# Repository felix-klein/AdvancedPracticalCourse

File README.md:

## Advanced Practical Course

**Info text Part II - Advanced Practical Course:** \
This project is the continuation of the Bachelor: An Integrated Approach to Predictive
Maintenance and Quality Control for E-Engines through Compliance Checking. The Advanced Practical Course: 0000000917
Advanced Practical Course - Supportive Process Automation and Worker Assistance (IN2128, IN2106), offers the
possibility to extend and improve the prototype on specific features. The GitHub environment is used for this part II
of the project for reasons of overview and deployment. This is done by redeploying and embedding directly. Note that
much of the previous information, implementations and structures are retained, but their form can and must be changed.
A special tagging of the changed items is not made explicit, but can be taken from the git history.

**Info text Part I - Bachelor Thesis:** \
Welcome to the system and documentation environment for the bachelor thesis: An Integrated Approach to Predictive 
Maintenance and Quality Control for E-Engines through Compliance Checking. In addition to the written thesis, this work
also includes the practical part of the prototype construction. This environment is primarily used for editing and 
storing the software used for the prototype, but also includes the thesis itself, the literature references, the 
artefacts and a large number of images and videos that exceed the scope of the written work. In the following, you will
be referred to the further materials and receive information about the systems and environments used.

# Bachelor Thesis Material
All non-software related materials can be found in the folder [Bachelor-Thesis-Material](Bachelor-Thesis-Material).
* [Artefacts](Bachelor-Thesis-Material/Artefacts)\
  Artefacts include data sheets and implementation recommendations for the hardware, as well as software packages and 
  descriptions for the Infineon microcontroller.
* [Images](Bachelor-Thesis-Material/Images)\
  Images are divided into two sections: Images that can be found in the written elaboration and images that have been 
  added as supplements.
* [Literature References](Bachelor-Thesis-Material/Literature_References)\
  The literature references are copies of the literature used in the preparation of this thesis.
* [Written Thesis](Bachelor-Thesis-Material/Written_Thesis)\
  In the Written Thesis environment, you will find the written bachelor thesis in PDF format, as well as photographs of
  the submitted portfolio.

# Requirements for easy set up
For a simple setup of this project, [pom.xml](pom.xml) can be used,
the dependencies and plugins contained here are as follows:

* Dependencies:
    * javafx-controls
    * javafx-fxml
    * jSerialComm
* Plugins:
    * javafx-maven-plugin
* Properties:
    * maven.compiler.source: 20
    * maven.compiler.target: 20
    * project.build.sourceEncoding: UTF-8

# IDE's and external usages
* External IDE`s:
  * Camunda Modeler (Version 5.12.0)
  * Arduino IDE (Version 2.2.1)
  * Gluon — Scene Builder (Version 20.0.0)
  * IntelliJ IDEA — Ultimate Edition (Version 2023.2.1)
  * CLion (Version 2023.2.1)
  * Postman (Version 10.19.0)

* External Additions:
  * [CPEE](https://cpee.org/) - Engine: Modeller for the processes
  * Google Chrome (Version 117.0.5938.149) - As standard browser

# Build and run the project
To get the project running:
1. Install Google Chrome;
2. Make *Maven* executable (run) by use of:\
   ```View > Tool Windows > Maven > i17BA > Run Configurations > i17BA [javafx:run]```

# Code structure and layout
The code structure in the form of classes, methods and attributes can quickly become confusing in such large projects.
Therefore, the following lightweight UML-diagram reveals a structural representation of the back-end. Even though not
all methods (and even classes) are shown, it still illustrates the key connections.

# Commands and Sensor Response rules and syntax
* Commands:
  * STI (Sensor-Time-Interval): ->sensorInterval
  * EST (Engine-Status-Type): 0/1
  * HDA (Hall-Delay-Angle): 1-59
  * RPM (Rotations-per-Minute): 0-4000
  * TMD (Time-Duration): 0-int (in seconds)
  * EMS (Emergency Stop): 1 -> Description at [Emergency Stop](#Emergency-Stop)
* Sensor Response:
  * TMP is a list of all the Temperature gathered.
  * VIB is a list of all the Vibration gathered.
  * MIC is a list of all the Microphone levels of loudness gathered.
  * CP1 is a list of all the sensor values at the Current-Phase-1.
  * CP2 is a list of all the sensor values at the Current-Phase-2.
  * CP3 is a list of all the sensor values at the Current-Phase-3.
  * TSP is a list of all the respective Time-Stamps gathered.
  * MIS is a list of all the Mission-Initialisation-Stamps (not corresponding to the rest).

# Blueprint hardware command initialisation (data structure)
* Pre-Testing (Each 1 - 9):
  * Cold_Start_Fast
  * Long_Run
  * Cool_Down_Fast
  * Cold_Start_Slow&G_C_Up
  * Cool_Down_Slow&G_C_Down
* See command structure and description in
  [BlueprintCommandFlowHardware_Described](src/main/resources/adminFiles/BlueprintCommandFlowHardware_Described.txt)

# Comment structure 
Comments are an important and essential part of clear and comprehensible code. Therefor, we do integrate comments
whenever there is a line of code which is not trivial.\
For further clarification and as a result of active programming we decided to use two types to comments:\
  * `//` for not completed comments and work, like a 'in construction comment'
  * `/* */` and `/** **/`for final comments and work, like a 'final/normal comment'
This structure does not count for code which is not written in java.

# List of Programming-References
* Arduino IDE-language: [Arduino LANGUAGE](https://www.arduino.cc/reference/en/)
* Arduino API List: [Arduino List Library  2.1.4](https://nkaaf.github.io/Arduino-List/html/index.html)
* Infineon Shield Examples: [Example Sketches](Bachelor-Thesis-Material/Artefacts/TLE9879QXA40/02_example_sketches)

# Design Guide
* Main Design-Guide reference:
  * [M2-Material Design](https://m2.material.io/design/color/dark-theme.html)
* Color Scheme Dark-Theme:
  * Color Scheme: [TUM Colors](https://gist.github.com/lnksz/51e3566af2df5c7aa678cd4dfc8305f7)
  * Dark Scheme: [MATERIAL DESIGN - Dark theme](https://m2.material.io/design/color/dark-theme.html#ui-application)
    * Dark: `#121212` - Background
    * TUM Blue: `#0065bd` - Header
    * tum-blue-dark: `#072140` - 
    * tum-grey-1: `#20252A` - Box
    * Red200: `#B00020` `176,0,32` - Warning, Wrong Task
    * Green200: `#018786` `1, 135, 134`- Correct Task
    * tum-blue-light: `#5E94D4` - Label, Event Start/End
    * tum-blue-light-dark: `#9ABCE4` - Event

# Hardware Connection
* Connection:
  * Type: `Cable`
  * Technique: `Serial` (JSerialComm)
  * Port: `/dev/cu.usbmodem141101`
  * Baud Rate: `9600`
  * Terminal Input: `screen /dev/cu.usbmodem141101 115200`
  * Main information Link: [JSerial GitHub](https://github.com/Fazecast/jSerialComm)

# Emergency Stop
The Emergency Stop is a Task which can be included into a process when ever needed.
Its primary function and intended use is the testing of a process flow. The user does
not need to delete or create a new whole process just for the testing of a beginning segment.

The Emergency Stop functions as a rapid and immediate end of the test. No more commands are
transferred to the board, the motor will stop running and the sensor data will stop sending.

# Further Code Insights as a Guest
As the main Git environment for the generation of this project, the [LRZ GitLab](https://gitlab.lrz.de)
is in use. Included is an extensive documentation of Commit, Push and Merge commands, as well as 
Milestones and Labels.\
As the publication requires a public availability of the system code and additional materials, the transit
to [GitHub i17ba](https://github.com/felix-klein/i17ba) was conducted and does not include properties which are not 
regarded directly to the systems, e.g. Push history and Milestones.\
If you are interested in further insights, older releases or development stages which are documented in the GitLab
version of this project, or if you got general project question, please use the 
Discord-Server: [Server i17ba-Q&A](https://discord.gg/rDpUg3Vh) (active until one year after official project completion, 15.10.2023).

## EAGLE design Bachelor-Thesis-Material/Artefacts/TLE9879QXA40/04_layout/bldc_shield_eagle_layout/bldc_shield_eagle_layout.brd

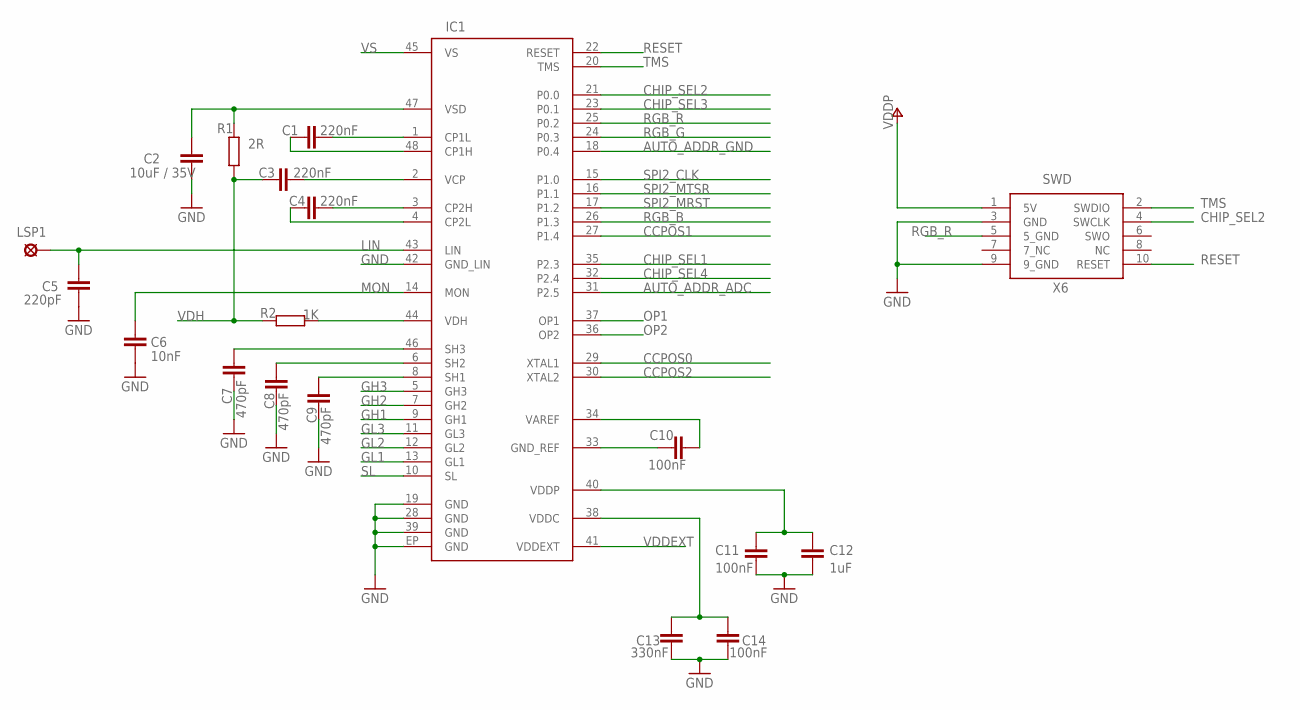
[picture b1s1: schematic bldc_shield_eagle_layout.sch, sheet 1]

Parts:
C1, C3, C4: 220nF; C0603
C2: 10uF / 35V; C1210; FARNELL 2112703RL
C5: 220pF; C0603
C6: 10nF; C0603
C7, C8, C9: 470pF; C0603
C10, C11, C14: 100nF; C0603
C12: 1uF; C0603
C13: 330nF; C0603
IC1: PROTEUS_EAGLE_TLE9879QX; VQFN48-15_7X7
INFINEONLOGO: INFINEON5; INFINEON_LOGO_5
LSP1: MCS10B
R1: 2R; R0603
R2: 1K; R0603
X6: SWD; FTSH-105-01-L-DH

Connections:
AUTO_ADDR_ADC: IC1.31 (P2.5); also elsewhere on the board
AUTO_ADDR_GND: IC1.18 (P0.4); also elsewhere on the board
CCPOS0: IC1.29 (XTAL1); also elsewhere on the board
CCPOS1: IC1.27 (P1.4); also elsewhere on the board
CCPOS2: IC1.30 (XTAL2); also elsewhere on the board
CHIP_SEL1: IC1.35 (P2.3); also elsewhere on the board
CHIP_SEL2: IC1.21 (P0.0), X6.4 (SWCLK); also elsewhere on the board
CHIP_SEL3: IC1.23 (P0.1); also elsewhere on the board
CHIP_SEL4: IC1.32 (P2.4); also elsewhere on the board
CP1H: C1.2, IC1.48 (CP1H)
CP1L: C1.1, IC1.1 (CP1L)
CP2H: C4.1, IC1.3 (CP2H)
CP2L: C4.2, IC1.4 (CP2L)
GH1: IC1.9 (GH1); also elsewhere on the board
GH2: IC1.7 (GH2); also elsewhere on the board
GH3: IC1.5 (GH3); also elsewhere on the board
GL1: IC1.13 (GL1); also elsewhere on the board
GL2: IC1.12 (GL2); also elsewhere on the board
GL3: IC1.11 (GL3); also elsewhere on the board
GND: C2.2, C5.1, C6.1, C7.2, C8.1, C9.1, C11.1, C12.1, C13.1, C14.1, IC1.19 (GND), IC1.28 (GND), IC1.39 (GND), IC1.42 (GND_LIN), IC1.EP (GND), X6.3 (GND), X6.9 (9_GND); also elsewhere on the board
GND_REF: C10.1, IC1.33 (GND_REF)
LIN: C5.2, IC1.43 (LIN), LSP1.MP
MON: C6.2, IC1.14 (MON)
OP1: IC1.37 (OP1); also elsewhere on the board
OP2: IC1.36 (OP2); also elsewhere on the board
RESET: IC1.22 (RESET), X6.10 (RESET); also elsewhere on the board
RGB_B: IC1.26 (P1.3); also elsewhere on the board
RGB_G: IC1.24 (P0.3); also elsewhere on the board
RGB_R: IC1.25 (P0.2), X6.5 (5_GND); also elsewhere on the board
SH1: C9.2, IC1.8 (SH1); also elsewhere on the board
SH2: C8.2, IC1.6 (SH2); also elsewhere on the board
SH3: C7.1, IC1.46 (SH3); also elsewhere on the board
SL: IC1.10 (SL); also elsewhere on the board
SPI2_CLK: IC1.15 (P1.0); also elsewhere on the board
SPI2_MRST: IC1.17 (P1.2); also elsewhere on the board
SPI2_MTSR: IC1.16 (P1.1); also elsewhere on the board
TMS: IC1.20 (TMS), X6.2 (SWDIO)
VAREF: C10.2, IC1.34 (VAREF)
VCP: C3.1, IC1.2 (VCP); also elsewhere on the board
VDDC: C13.2, C14.2, IC1.38 (VDDC)
VDDEXT: IC1.41 (VDDEXT); also elsewhere on the board
VDDP: C11.2, C12.2, IC1.40 (VDDP), X6.1 (5V); also elsewhere on the board
VDH: C3.2, R1.2, R2.2; also elsewhere on the board
VDH_CHIP: IC1.44 (VDH), R2.1
VS: IC1.45 (VS); also elsewhere on the board
VSD: C2.1, IC1.47 (VSD), R1.1

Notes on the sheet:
RGB_R

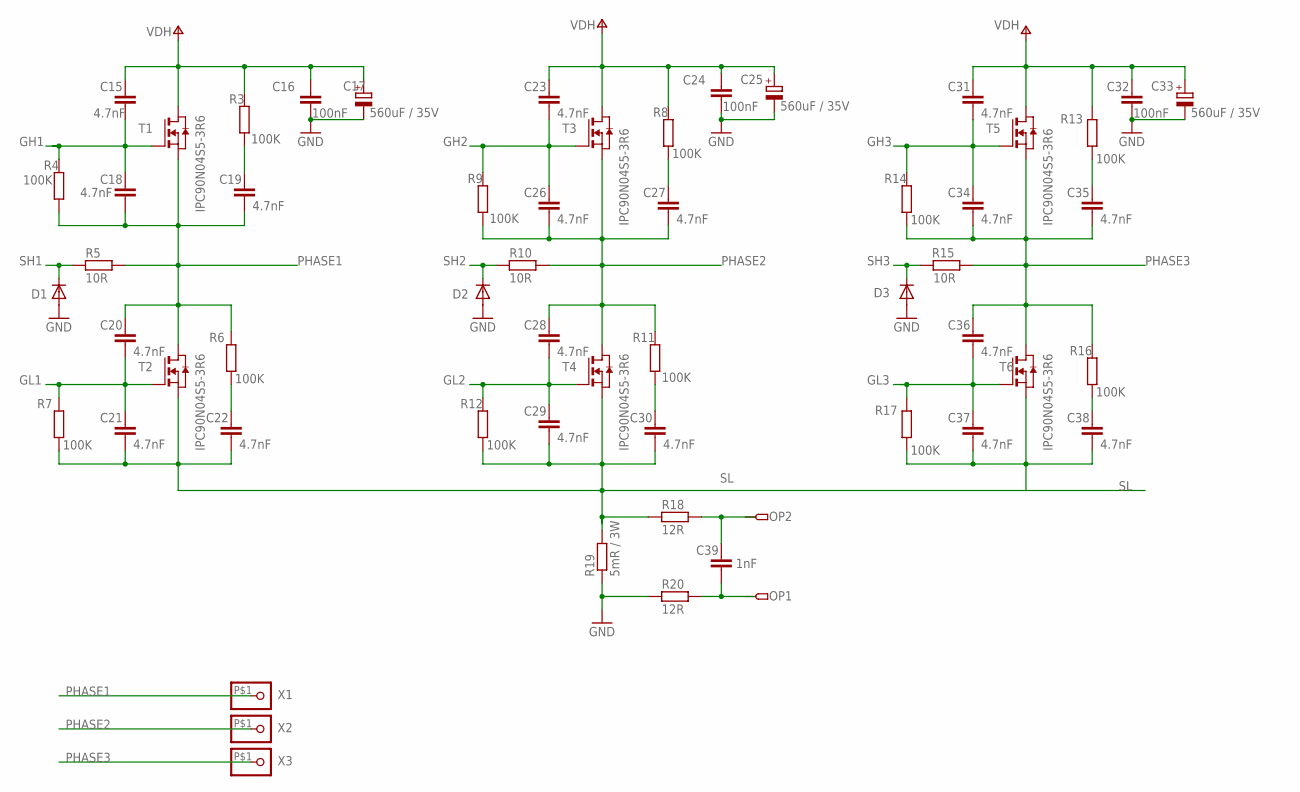
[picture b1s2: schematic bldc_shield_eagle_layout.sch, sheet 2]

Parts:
C15, C18, C19, C20, C21, C22, C23, C26, C27, C28, C29, C30, C31, C34, C35, C36, C37, C38: 4.7nF; C0603
C16, C24, C32: 100nF; C0603
C17, C25, C33: 560uF / 35V; 153CLV-1014; FARNELL 2408677
C39: 1nF; C0603
D1, D2, D3: DIODE-SOD323-W; SOD323-W
R3, R4, R6, R7, R8, R9, R11, R12, R13, R14, R16, R17: 100K; R0603
R5, R10, R15: 10R; R0603
R18, R20: 12R; R0603
R19: 5mR / 3W; R6332
T1, T2, T3, T4, T5, T6: IPC90N04S5-3R6; PG-TDSON-8
X1, X2, X3: SCREWHOLE

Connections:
GH1: C15.2, C18.1, R4.2, T1.4 (G); also elsewhere on the board
GH2: C23.2, C26.1, R9.2, T3.4 (G); also elsewhere on the board
GH3: C31.2, C34.1, R14.2, T5.4 (G); also elsewhere on the board
GL1: C20.2, C21.1, R7.2, T2.4 (G); also elsewhere on the board
GL2: C28.2, C29.1, R12.2, T4.4 (G); also elsewhere on the board
GL3: C36.2, C37.1, R17.2, T6.4 (G); also elsewhere on the board
GND: C16.2, C17.-, C24.2, C25.-, C32.2, C33.-, D1.A, D2.A, D3.A, R19.1, R20.2; also elsewhere on the board
unnamed: C19.1, R3.1
unnamed: C22.1, R6.1
unnamed: C27.1, R8.1
unnamed: C30.1, R11.1
unnamed: C38.1, R16.1
unnamed: C35.1, R13.1
OP1: C39.2, R20.1; also elsewhere on the board
OP2: C39.1, R18.1; also elsewhere on the board
PHASE1: C18.2, C19.2, C20.1, R4.1, R5.1, R6.2, T1.1 (S), T1.2 (S), T1.3 (S), T2.5 (D), T2.6 (D), T2.7 (D), T2.8 (D), T2.D, X1.P$1
PHASE2: C26.2, C27.2, C28.1, R9.1, R10.1, R11.2, T3.1 (S), T3.2 (S), T3.3 (S), T4.5 (D), T4.6 (D), T4.7 (D), T4.8 (D), T4.D, X2.P$1
PHASE3: C34.2, C35.2, C36.1, R14.1, R15.1, R16.2, T5.1 (S), T5.2 (S), T5.3 (S), T6.5 (D), T6.6 (D), T6.7 (D), T6.8 (D), T6.D, X3.P$1
SH1: D1.C, R5.2; also elsewhere on the board
SH2: D2.C, R10.2; also elsewhere on the board
SH3: D3.C, R15.2; also elsewhere on the board
SL: C21.2, C22.2, C29.2, C30.2, C37.2, C38.2, R7.1, R12.1, R17.1, R18.2, R19.2, T2.1 (S), T2.2 (S), T2.3 (S), T4.1 (S), T4.2 (S), T4.3 (S), T6.1 (S), T6.2 (S), T6.3 (S); also elsewhere on the board
VDH: C15.1, C16.1, C17.+, C23.1, C24.1, C25.+, C31.1, C32.1, C33.+, R3.2, R8.2, R13.2, T1.5 (D), T1.6 (D), T1.7 (D), T1.8 (D), T1.D, T3.5 (D), T3.6 (D), T3.7 (D), T3.8 (D), T3.D, T5.5 (D), T5.6 (D), T5.7 (D), T5.8 (D), T5.D; also elsewhere on the board

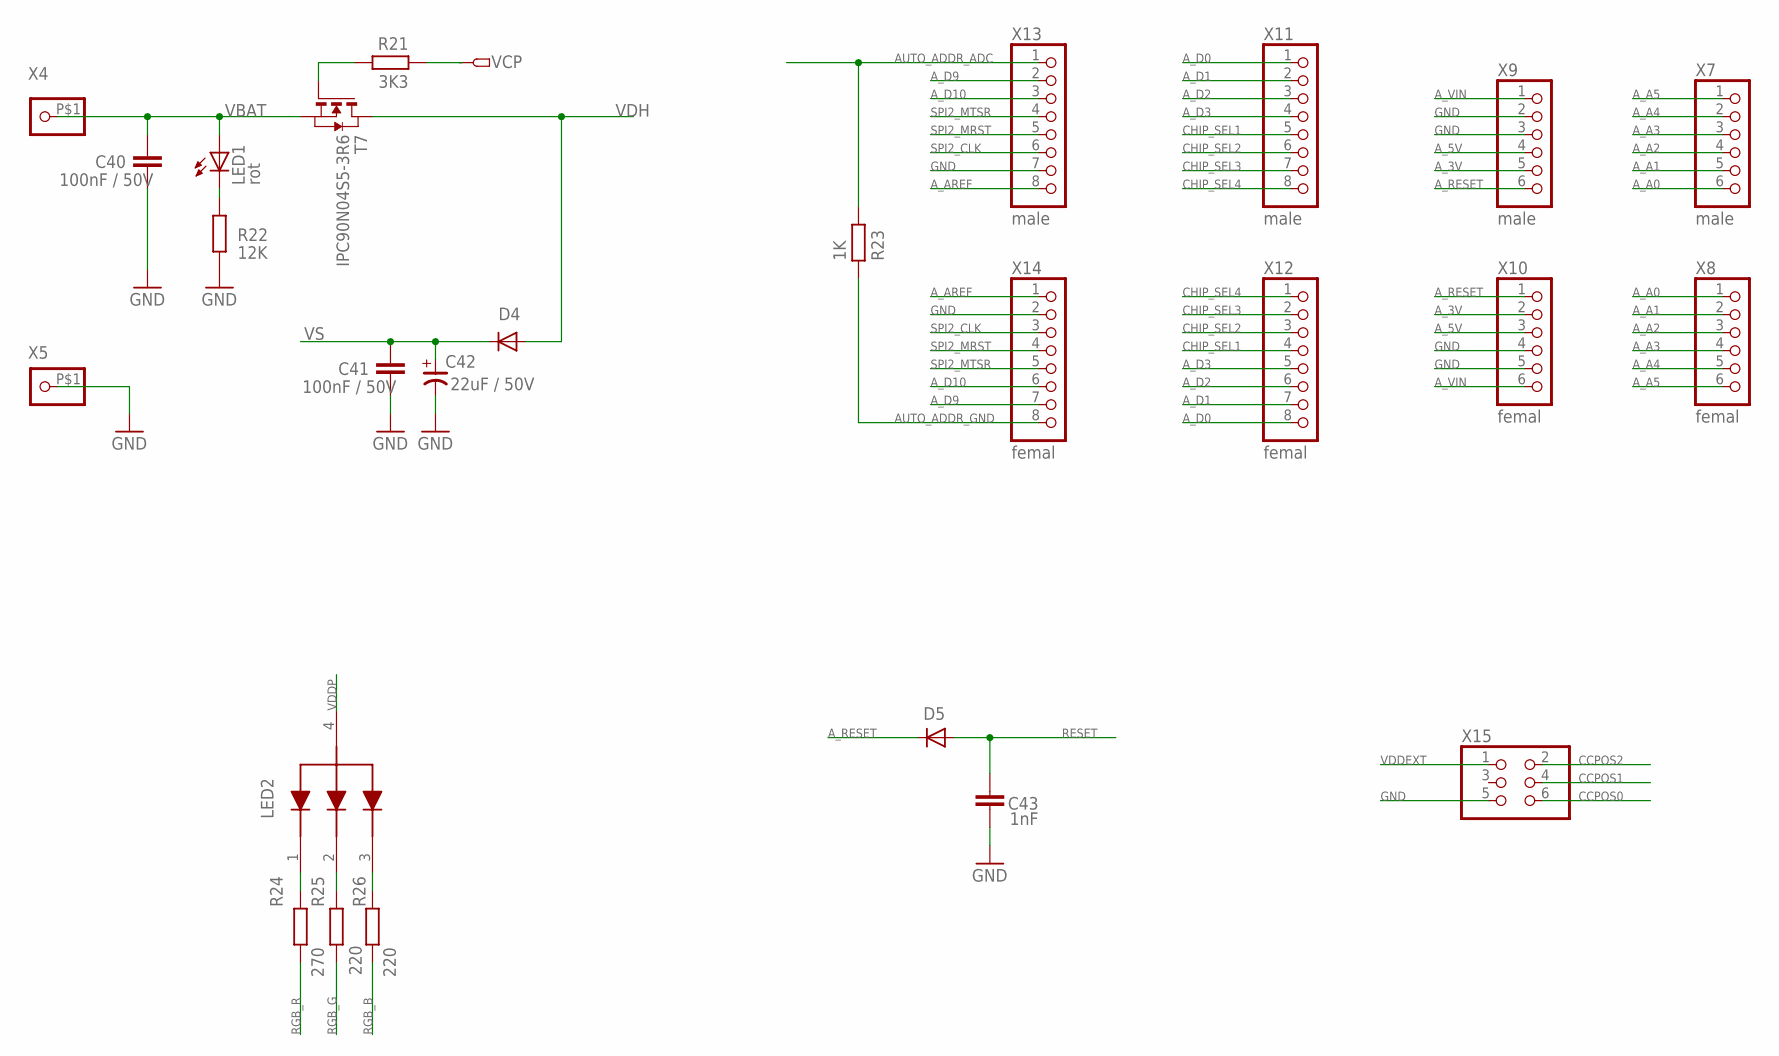
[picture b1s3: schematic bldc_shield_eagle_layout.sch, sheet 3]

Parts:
C40, C41: 100nF / 50V; C0603; FARNELL 1740621
C42: 22uF / 50V; 153CLV-0505; FARNELL 2408669
C43: 1nF; C0603
D4: DIODE_DIODE-SOD123; DIODE_SOD123
D5: DIODE-SOD323-W; SOD323-W
LED1: rot; SML0603; FARNELL 2112124
LED2: RGB_LED; LTST-C19HE1WT
R21: 3K3; R0603
R22: 12K; R0603
R23: 1K; R0603
R24: 270; R0603
R25, R26: 220; R0603
T7: IPC90N04S5-3R6; PG-TDSON-8
X4, X5: SCREWHOLE
X7, X9: male; 1X06SMD
X8, X10: femal; 1X06SMD-FEMAL
X11, X13: male; 1X08SMD
X12, X14: femal; 1X08SMD-FEMAL
X15: PINHD-2X3_2.54-90°; 2X03/90

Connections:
AUTO_ADDR_ADC: R23.2, X13.1; also elsewhere on the board
AUTO_ADDR_GND: R23.1, X14.8; also elsewhere on the board
A_3V: X9.5, X10.2
A_5V: X9.4, X10.3
A_A0: X7.6, X8.1
A_A1: X7.5, X8.2
A_A2: X7.4, X8.3
A_A3: X7.3, X8.4
A_A4: X7.2, X8.5
A_A5: X7.1, X8.6
A_AREF: X13.8, X14.1
A_D0: X11.1, X12.8
A_D1: X11.2, X12.7
A_D2: X11.3, X12.6
A_D3: X11.4, X12.5
A_D9: X13.2, X14.7
A_D10: X13.3, X14.6
A_RESET: D5.C, X9.6, X10.1
A_VIN: X9.1, X10.6
CCPOS0: X15.6; also elsewhere on the board
CCPOS1: X15.4; also elsewhere on the board
CCPOS2: X15.2; also elsewhere on the board
CHIP_SEL1: X11.5, X12.4; also elsewhere on the board
CHIP_SEL2: X11.6, X12.3; also elsewhere on the board
CHIP_SEL3: X11.7, X12.2; also elsewhere on the board
CHIP_SEL4: X11.8, X12.1; also elsewhere on the board
GND: C40.2, C41.2, C42.-, C43.1, R22.2, X5.P$1, X9.2, X9.3, X10.4, X10.5, X13.7, X14.2, X15.5; also elsewhere on the board
unnamed: LED2.2, R25.1
unnamed: LED2.1, R24.1
unnamed: LED2.3, R26.1
unnamed: R21.2, T7.4 (G)
unnamed: LED1.C, R22.1
RESET: C43.2, D5.A; also elsewhere on the board
RGB_B: R26.2; also elsewhere on the board
RGB_G: R25.2; also elsewhere on the board
RGB_R: R24.2; also elsewhere on the board
SPI2_CLK: X13.6, X14.3; also elsewhere on the board
SPI2_MRST: X13.5, X14.4; also elsewhere on the board
SPI2_MTSR: X13.4, X14.5; also elsewhere on the board
VBAT: C40.1, LED1.A, T7.1 (S), T7.2 (S), T7.3 (S), X4.P$1
VCP: R21.1; also elsewhere on the board
VDDEXT: X15.1; also elsewhere on the board
VDDP: LED2.4; also elsewhere on the board
VDH: D4.A, T7.5 (D), T7.6 (D), T7.7 (D), T7.8 (D), T7.D; also elsewhere on the board
VS: C41.1, C42.+, D4.C; also elsewhere on the board

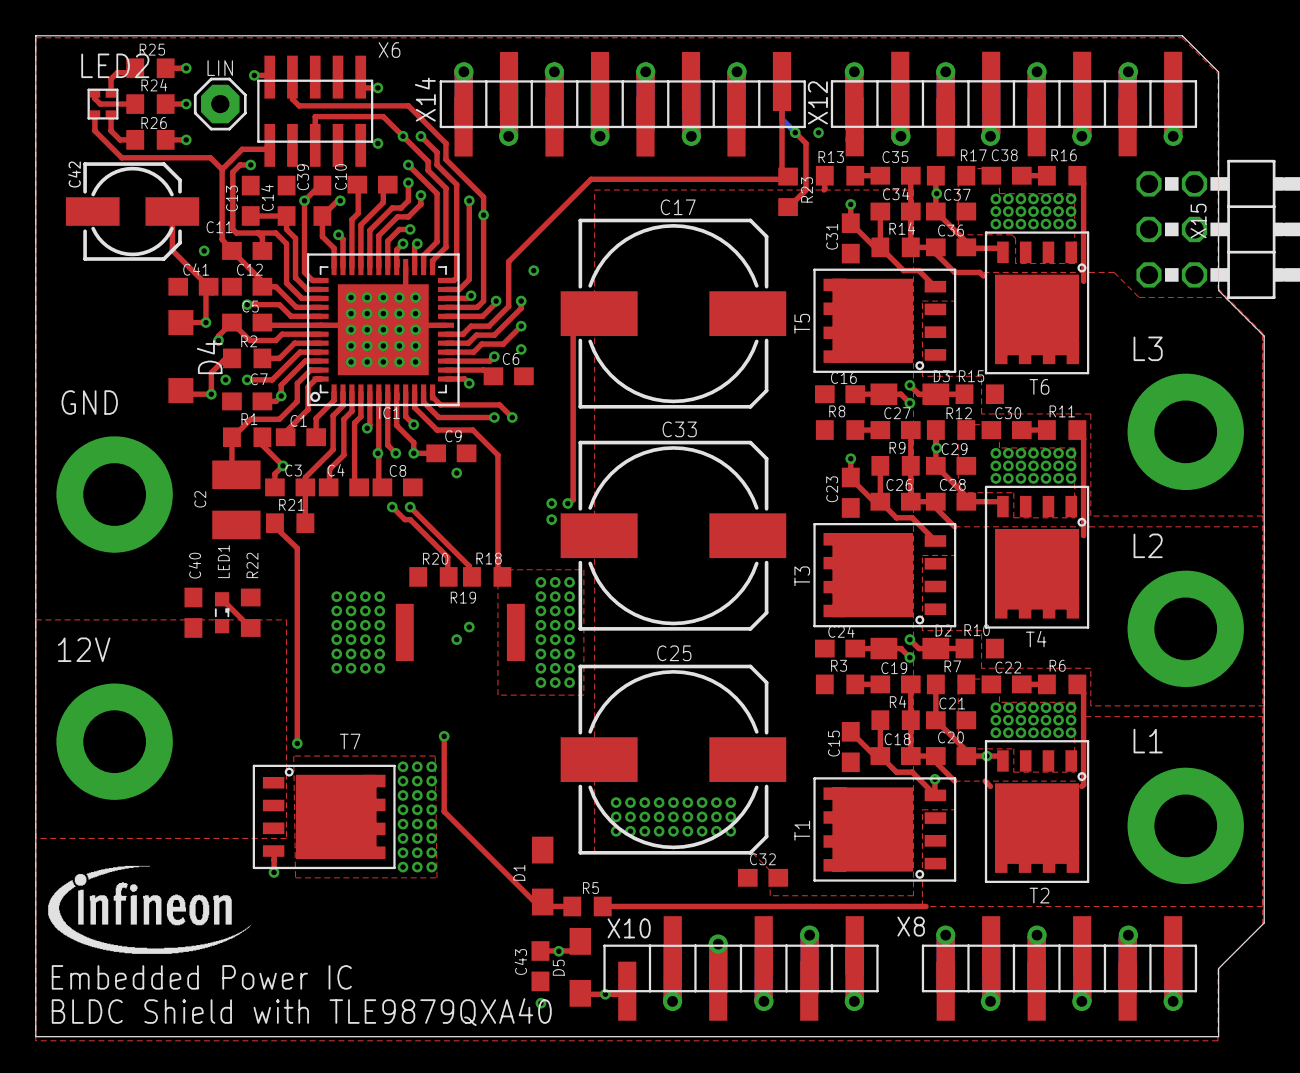
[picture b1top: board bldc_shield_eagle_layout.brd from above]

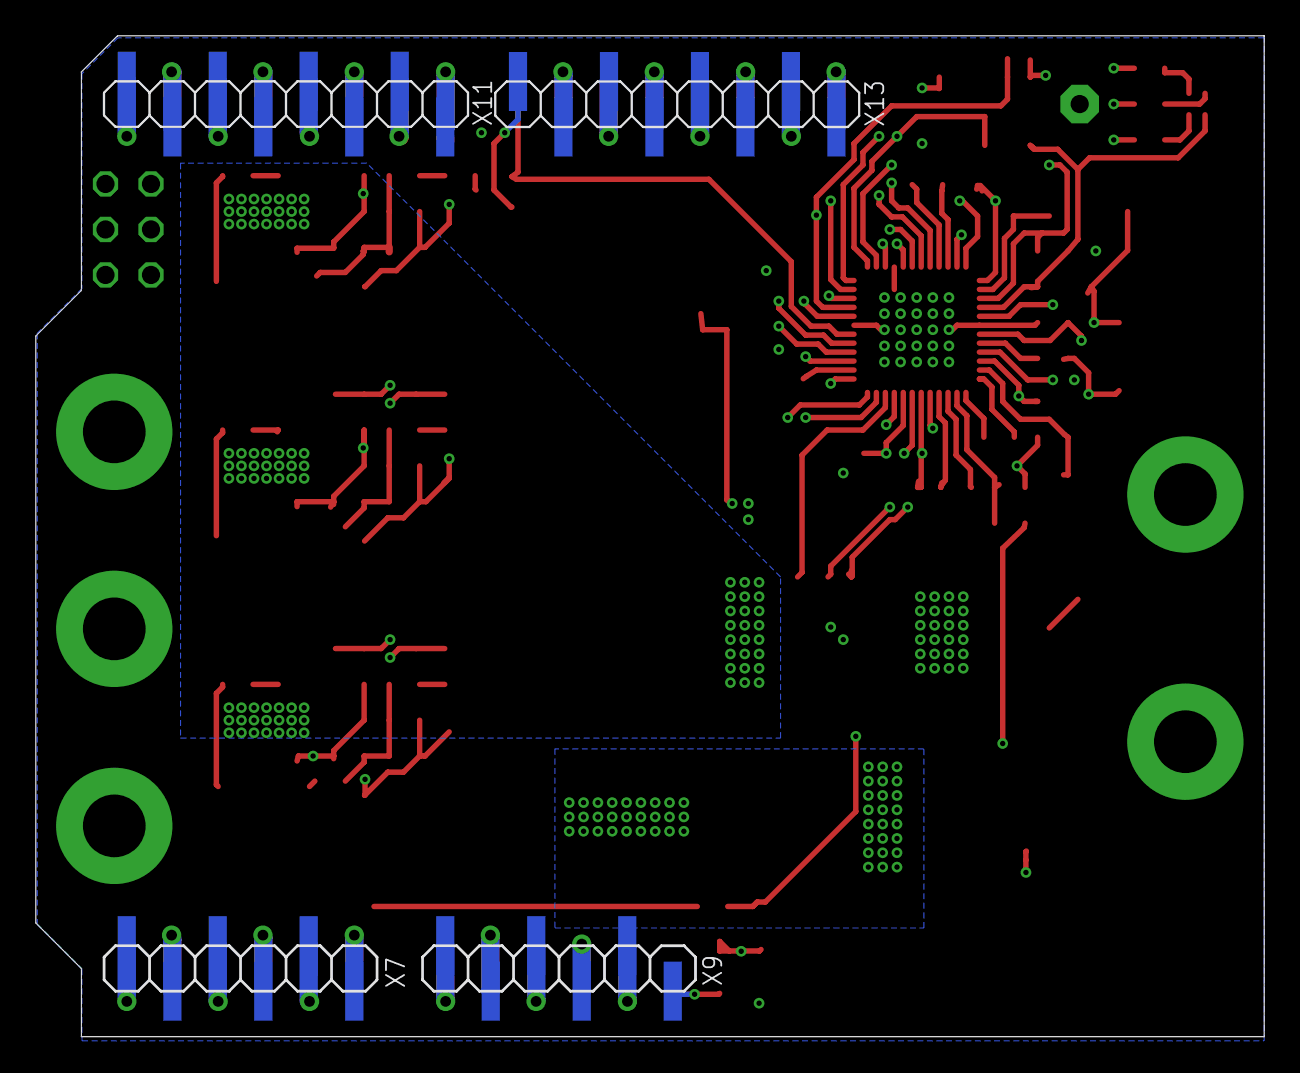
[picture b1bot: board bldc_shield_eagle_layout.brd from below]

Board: 4 copper layers, 68.6 x 55.9 mm, 101 parts (4 on the bottom side), 78 nets.

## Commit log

2023-06-24 Structural changes and implementations like JavaFX, JUnit, Camunda, jSerialComm and exemplary code.
2023-06-25 Additions to the pom.xml and the creation of a README.md.
2023-06-25 New Structuring of the MainApplication.java and the creation/integration of UML.png.
2023-06-27 Redesign of the BPMN environment and handling. The pom.xml is now more lightweight but the user need`s to implement a separate Camunda Modeler App.
2023-06-27 Clean-up in the program and ready to merge to the main branch.
2023-06-27 JavaFX experimentations and first integrations. It was also changed to use SceneBuilder for operating designs.
2023-06-28 Scene Creator frontend/layout modifications and first style changes.
2023-06-29 The scene was adjusted and complemented. There is also a separate Admin Scene. The code is more lightweight now and reduces duplicates as much as possible. Warning: The Admin page does have a problem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
2023-06-30 The frontend is extended with further functionality. The Camunda Modeler files are included and the app opens by request. Files Long-Run and Short-Run are not complete, but that needs to be done if w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
2023-07-01 Admin page structure is completed including modifications to the user side. We include now more functional and operating structure, as well as first rerouting operations. We consider to add a result 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
2023-07-01 The data processing does include all new objects and classes needed to order the Process Data for further investigation and operations. As an addition, Unversioned Files appeared which could have an 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
2023-07-02 The data processing is for the first part complete. It was tested lightweight via prints. The result is a data type tree structure, including all the information directly or with code numbers. All in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
2023-07-02 Small changes and actualisation's in the UML.svg file for the transparency.
2023-07-03 Addendum/Improvement: We forgot to implement the Gateway node. As a result, did we add it to all areas where needed and we adjusted the UML diagram as well.
2023-07-03 Addendum/Improvement: Logical adjustment in the sense of accepting Exclusive gateways, with specific rules, for easier loop handling.
2023-07-07 Process Mining and advanced! The goal was to implement the pm package but the data was unclear. This session resulted in an overall session including changes in nearly all related areas. Most importa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
2023-07-07 Adjustments related to the lates chaotic commit (push). More style and logical adjustments.
2023-07-10 Adjustments with no operational or structural influence.
2023-07-10 Small Admin adjustments and logical structuring.
2023-07-10 Small Admin adjustments and form related contributions to reduce errors.
2023-07-10 Adjustments to warnings and the change of Camunda Modeler opener method to eliminate the warnings and to modernize the API.
2023-07-11 Big steps into the data saving, loading and changing of .txt data. Adjustments to the admin frontend and the handling of those new options. The Connection area got bigger for the moment but will be o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
2023-07-14 Untested steps into the data processing and connection to the hardware. New classes and Resources for the storing and processing of the sensor data. Tests are still be needed and are in process.
2023-07-14 Not finished or tested commit, with the goal of saving the current stage. There are mostly structural changes for more logical and cleaner functions.
2023-07-15 Not finished work session, but with improvements for the Serial communication and the style of data preparation and structuring.
2023-07-16 Finished code for the FIRST DRAFT, but still without a test. Inclusion of the arduino board code.
2023-07-16 First Test: Board-Test separate with Serial messages per hand. Bug fixes with correcting results. -> Result Notice: the memory at the board is very small!
2023-07-17 CODE RUNNING and WORKING: The board connection is working and the data is transferred correctly. Loops still need to be tested.
2023-07-17 The Hardware connection and its data transfer is achieved. Loops as well as normal processes are tested and the data is saved. Adjustments in the data preparations for the statistics and the mathemat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
2023-07-17 Small style, READ.ME and warning adjustments to make the code more readable and clean.
2023-07-18 Major changes to the BordCode.ino to adjust it to the Infineon board. This does include research and results in motor control parameter and other structures. Modifications in style related areas wher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
2023-07-18 Untested Changes to the data processing and file creation of the blueprint data. Adding of an additional variable for the analyses of the processed missions.
2023-07-18 Tested file writing functions and return data ordering. Out-commenting is temporary for reasons of easier testing.
2023-07-18 Adjustment of the latest changes to the UML diagram.
2023-07-20 Changes to the clean structure and visualisation. No rudimentary changes but rather a cleanup for the presentation to the coordinator. Last push before the exams brake.
2023-09-04 Changes and clean up for a clean rebuild of the new branch.
2023-09-04 Creation of THE SWITCH - PREP, to adjust the code and its structure for the rebuilding phase including a new Process Modeler.
2023-09-04 First changes to the frontend structure and the inclusion of the Process JavaFX interface. Still not working but we consider a first save for refactoring.
2023-09-04 Partly working web view with the wrong browser. The Overall view is correct.
2023-09-12 The main change of The Switch, with changes of the data receiving and data processing. It still needs a lot of changes and especially testing.
2023-09-14 Adjustments and further changes which are a result of the new modeler. The Terminal and the blueprint was adjusted as well.
2023-09-14 Completed TheSwitch without testing and test runs. Modifications in nearly all classes and the deletion of the package datapreparation.
2023-09-14 UML adjustments for the correct documentation.
2023-09-14 Changes doe to new ideas for the model representation and preparation for the analyses start.
2023-09-14 ReadMe adjustments recording to the new changes.
2023-09-14 Preparation for the analysis phase.
2023-09-15 Major changes to the blueprint aspect and the creation of a corresponding command file for the admin blueprint initialisation.
2023-09-29 The data comparison and saving is adjusted and build. The next phase is the reals Checking of the compliance and its savings in a meaningful manner.
2023-10-03 IN the middle of the sensor data per second comparison and shortly before the mathematical evaluation.
2023-10-03 Major changes to the User Scene with the adding of customizable deviation and acceptance.
2023-10-03 Final implementations and adjustments to the calculation of the compliance checking. -> Compliance Checking Algorithm.
2023-10-04 User Interface adjustments: Selection increase, Process Creation, Process Visualization, Test Result structure. First Test for the data gathering are started in a not engine like manner.
2023-10-04 First serialisation tests and adjustments to the hardware.
2023-10-08 Adjustments and new structures after FIRST PRACTICAL TESTS. Admin side with complete practical tests. New structure in data analyses and processing.
2023-10-10 Further testing to the analysis area.
2023-10-10 pom.xml cleanup.
2023-10-10 Adjustments and corrections after further tests.
2023-10-10 Further Tests and Adjustments. Further functions for the analysis.
2023-10-11 Further Tests and Adjustments. Further functions for the analysis. (2)
2023-10-12 First positive motor test.
2023-10-13 Creation of the Analysis Interface and adding modifications.
2023-10-13 Creation of the Analysis Interface and adding modifications. New structure and final preparation of the README.md file.
2023-10-13 Modification of additional material.
2023-10-14 Adjustments to the Hardware code, and minor bug fixes.
2023-10-15 (2) Adjustments to the Hardware code, and minor bug fixes.
2023-10-15 (3) Adjustments to the Hardware code, and minor bug fixes. README.md adjustments.
2023-10-15 (4) Adjustments to the Hardware code, and minor bug fixes. README.md adjustments.
2023-10-15 (5) Adjustments to the Hardware code, and minor bug fixes. Major style changes.
2023-10-15 (6) Adjustments to the Hardware code, and minor bug fixes. Additional material.
2023-10-15 Initialisation of a Blueprint Engine for further Testing as an Example
2023-11-13 Initialisation and Project Start: This first push establishes the GitHub connection and changes the ReadMe as the new Part II of this project.
